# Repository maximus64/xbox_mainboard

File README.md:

# Xbox Original Mainboard Reverse Engineering

This project is an attempt to recreate the Xbox 1.6 mainboard in Kicad. The first goal is to recreate the layout of the PCB then recover the netlist then draw the schematic.

Note: [Custom version of Kicad](https://github.com/maximus64/kicad/tree/maximus/xbox_project) are required to load this project. The official version of Kicad has bitmap surface cache size limmiter and stores bitmap data as base64 encoded data. The patch removes the surface cache size constraint and just stores the image path rather than the store the bitmap data as base64 encoding. This is done to enhance performance so that Kicad can display the board scan overlay and re-trace the mainboard layout.

## Board scan

Scan image of all the copper layers is in kicad/xbox_1.6/board_scan/1.6

### PCB stackup

1. Signal
2. Ground
3. Power
4. Signal

### Progress

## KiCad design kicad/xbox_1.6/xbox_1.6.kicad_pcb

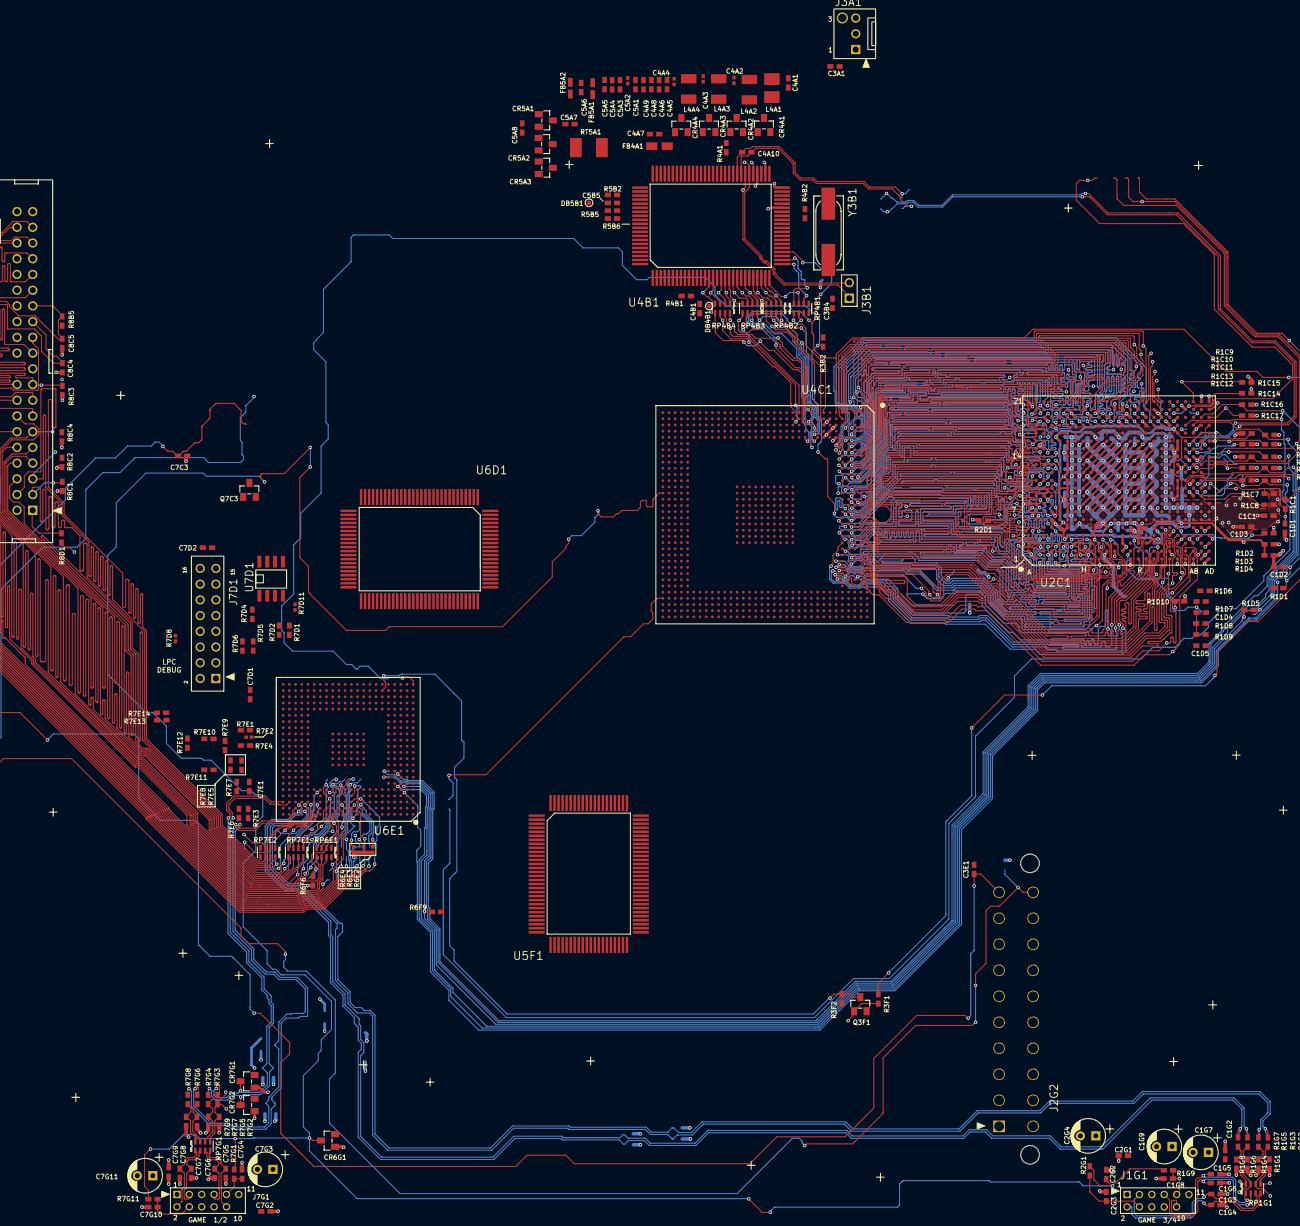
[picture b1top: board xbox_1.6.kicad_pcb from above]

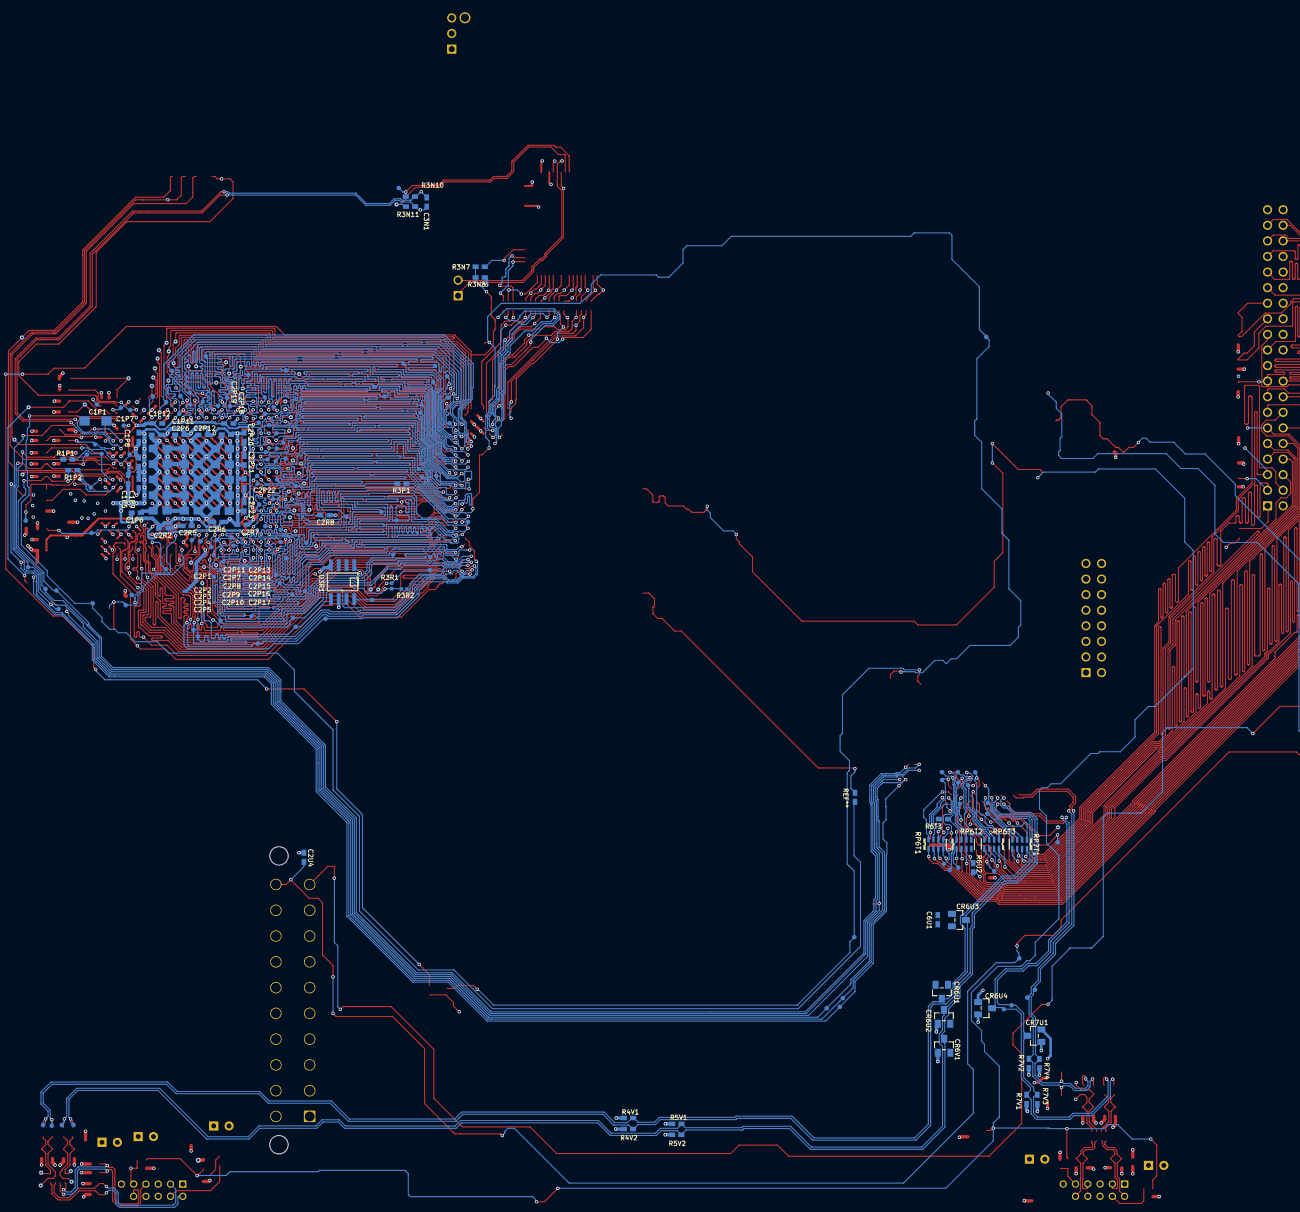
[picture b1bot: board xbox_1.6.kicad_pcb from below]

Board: 4 copper layers, 261 parts (69 on the bottom side), 273 nets.

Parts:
C1C1, C1D1, C1D2, C1D3, C1D4, C1D5, C1G2, C1G3, C1G4, C1G5, C1G6, C1G8, C1P5, C1P6, C1P7, C1P8, C1P9, C1P11, C1P12, C2G1, C2G2, C2G3, C2P6, C2P12, C2P18, C2P19, C2P20, C2P21, C2P22, C2P23, C2R2, C2R5, C2R6, C2R7, C2R8, C2U4, C3A1, C3B4, C3E1, C3N1, C4A1, C4A5, C4A6, C4A7, C4A8, C4A9, C4A10, C4B1, C5A1, C5A3, C5A4, C5A5, C5A6, C5A7, C5A8, C5B5, C6U1, C7C3, C7D1, C7D2, C7E1, C7G2, C7G4, C7G5, C7G6, C7G7, C7G8, C7G9, C7G10, C8C4, C8C5: 0603_smd
C1G7, C1G9, C2G4, C7G3, C7G11: CP_Radial_Tantal_D5.5mm_P2.50mm
C1P1: 1206_smd
C2P1, C2P2, C2P3, C2P4, C2P5, C2P7, C2P8, C2P9, C2P10, C2P11, C2P13, C2P14, C2P15, C2P16, C2P17: 0805_smd
C4A2, C4A3, C4A4, C5A2: 0402_smd
CR4A1, CR4A2, CR4A3, CR4A4, CR5A1, CR5A2, CR5A3, CR6G1, CR6U1, CR6U2, CR6U3, CR6U4, CR6V1, CR7G1, CR7G2, CR7U1: SOT-23
DB4B1, DB5B1: TP
FB4A1: fb_2_smd
FB5A1, FB5A2: fb_1_smd
J1G1, J7G1: jst_phd_12
J2G2: ATX_20PIN
J3A1: fan_connector
J3B1: PinHeader_1x02_P2.54mm_Vertical
J7D1: LPC_16_Pin
J8C1: IDC_40_Pin
L4A1: inductor_1210_bigpad_smd
L4A2, L4A3, L4A4: inductor_1210_smd
Q3F1, Q7C3: SOT-23
R1C1, R1C2, R1C3, R1C4, R1C5, R1C6, R1C7, R1C8, R1C9, R1C10, R1C11, R1C12, R1C13, R1C14, R1C15, R1C16, R1C17, R1D1, R1D2, R1D3, R1D4, R1D5, R1D6, R1D7, R1D8, R1D9, R1D10, R1G1, R1G2, R1G3, R1G4, R1G5, R1G6, R1G7, R1G8, R1G9, R1P1, R1P2, R2D1, R2G1, R3B2, R3F1, R3F2, R3N7, R3N8, R3N10, R3N11, R3P1, R4A1, R4B1, R4B2, R4V1, R4V2, R5B2, R5B5, R5B6, R5V1, R5V2, R6F6, R6F9, R6T3, R6U2, R7D1, R7D2, R7D4, R7D5, R7D6, R7E1, R7E3, R7E4, R7E5, R7E6, R7E7, R7E8, R7E9, R7E10, R7E11, R7E12, R7E13, R7E14, R7G1, R7G2, R7G3, R7G4, R7G5, R7G6, R7G7, R7G8, R7G9, R7G11, R7V1, R7V2, R7V3, R7V4, R8B5, R8C1, R8C2, R8C3, R8C4, R8D1: 0603_smd
R3R1, R3R2, R6E2, R6E3, R6E4, R7D8, R7D11, R7E2: 0402_smd
RP1G1, RP4B1, RP4B2, RP4B3, RP4B4, RP6E1, RP6T1, RP6T2, RP6T3, RP7E1, RP7E2, RP7G1, RP7T1: 0603_4_array
RT5A1: rt_1_smd
U2C1: intel_495_bga2
U3R1, U7D1: SOIC8
U4B1, U5F1, U6D1: ddr_100_tqfp
U4C1: nvidia_xgpu_nv2a
U6E1: nvidia_mcpx
Y3B1: Crystal_SMD_HC49-SD

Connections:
/5V: C7G2.1, C7G3.1, C7G9.1, C7G11.1, J2G2.15, J7G1.1, J7G1.8
/5V_STB: J2G2.1, J2G2.2, J2G2.3, J2G2.13
/CPU_A3: U2C1.L3, U4C1.B22
/CPU_A4: U2C1.K3, U4C1.A19
/CPU_A5: U2C1.J2, U4C1.D27
/CPU_A6: U2C1.L4, U4C1.A22
/CPU_A7: U2C1.L1, U4C1.C21
/CPU_A8: U2C1.K5, U4C1.A20
/CPU_A9: U2C1.K1, U4C1.B20
/CPU_A10: U2C1.J1, U4C1.A18
/CPU_A11: U2C1.J3, U4C1.B18
/CPU_A12: U2C1.K4, U4C1.C19
/CPU_A13: U2C1.G1, U4C1.C17
/CPU_A14: U2C1.H1, U4C1.A17
/CPU_A15: U2C1.E4, U4C1.D19
/CPU_A16: U2C1.F1, U4C1.A16
/CPU_A17: U2C1.F4, U4C1.D21
/CPU_A18: U2C1.F2, U4C1.C24
/CPU_A19: U2C1.E1, U4C1.E26
/CPU_A20: U2C1.C4, U4C1.E20
/CPU_A20M: R1P2.2, U2C1.AD10
/CPU_A20M_R: R1C6.1, R1P2.1, U6E1.H4
/CPU_A21: U2C1.D3, U4C1.E25
/CPU_A22: U2C1.D1, U4C1.D25
/CPU_A23: U2C1.E2, U4C1.C26
/CPU_A24: U2C1.D5, U4C1.E19
/CPU_A25: U2C1.D4, U4C1.C20
/CPU_A26: U2C1.C3, U4C1.E21
/CPU_A27: U2C1.C1, U4C1.E23
/CPU_A28: U2C1.B3, U4C1.C22
/CPU_A29: U2C1.A3, U4C1.B16
/CPU_A30: U2C1.B2, U4C1.E24
/CPU_ADS: U2C1.AB2, U4C1.B27
/CPU_BCLK: R3R1.2, R3R2.1, U2C1.M3
/CPU_BCLK_R: R3R1.1, U3R1.1, U4C1.C29
/CPU_BCLK_R2: R3R2.2, U3R1.8
/CPU_BNR: U2C1.T4, U4C1.C23
/CPU_BPRI: U2C1.U4, U4C1.E28
/CPU_BREQ0: R2D1.2, U2C1.C6
/CPU_BSEL0: R1C4.1, U2C1.AA12
/CPU_BSEL1: R1C10.1, U2C1.AB15
/CPU_CLKREF: C1D4.1, R1D8.1, R1D9.1, U2C1.P2
/CPU_D0: U2C1.D10, U4C1.A13
/CPU_D1: U2C1.D11, U4C1.D17
/CPU_D2: U2C1.C7, U4C1.E18
/CPU_D3: U2C1.C8, U4C1.E17
/CPU_D4: U2C1.B9, U4C1.A14
/CPU_D5: U2C1.A9, U4C1.B14
/CPU_D6: U2C1.C10, U4C1.A12
/CPU_D7: U2C1.B11, U4C1.B12
/CPU_D8: U2C1.C12, U4C1.C16
/CPU_D9: U2C1.B13, U4C1.A10
/CPU_D10: U2C1.A14, U4C1.A9
/CPU_D11: U2C1.B12, U4C1.E16
/CPU_D12: U2C1.E12, U4C1.A15
/CPU_D13: U2C1.B16, U4C1.C13
/CPU_D14: U2C1.A13, U4C1.B10
/CPU_D15: U2C1.D13, U4C1.C15
/CPU_D16: U2C1.D15, U4C1.E14
/CPU_D17: U2C1.D12, U4C1.D15
/CPU_D18: U2C1.B14, U4C1.C9
/CPU_D19: U2C1.E14, U4C1.C14
/CPU_D20: U2C1.C13, U4C1.A11
/CPU_D21: U2C1.A19, U4C1.C8
/CPU_D22: U2C1.B17, U4C1.A8
/CPU_D23: U2C1.A18, U4C1.E12
/CPU_D24: U2C1.C17, U4C1.E13
/CPU_D25: U2C1.D17, U4C1.D13
/CPU_D26: U2C1.C18, U4C1.A7
/CPU_D27: U2C1.B19, U4C1.C12
/CPU_D28: U2C1.D18, U4C1.B8
/CPU_D29: U2C1.B20, U4C1.B6
/CPU_D30: U2C1.A20, U4C1.A6
/CPU_D31: U2C1.B21, U4C1.A5
/CPU_D32: U2C1.D19, U4C1.E11
/CPU_D33: U2C1.C21, U4C1.C10
/CPU_D34: U2C1.E18, U4C1.E9
/CPU_D35: U2C1.C20, U4C1.D11
/CPU_D36: U2C1.F19, U4C1.C7
/CPU_D37: U2C1.D20, U4C1.D9
/CPU_D38: U2C1.D21, U4C1.E10
/CPU_D39: U2C1.H18, U4C1.C11
/CPU_D40: U2C1.F18, U4C1.E8
/CPU_D41: U2C1.J18, U4C1.C2
/CPU_D42: U2C1.F21, U4C1.A3
/CPU_D43: U2C1.E20, U4C1.B4
/CPU_D44: U2C1.H19, U4C1.A1
/CPU_D45: U2C1.E21, U4C1.A4
/CPU_D46: U2C1.J20, U4C1.C6
/CPU_D47: U2C1.H21, U4C1.B2
/CPU_D48: U2C1.L18, U4C1.C1
/CPU_D49: U2C1.G20, U4C1.C3
/CPU_D50: U2C1.P18, U4C1.E6
/CPU_D51: U2C1.G21, U4C1.A2
/CPU_D52: U2C1.K18, U4C1.E7
/CPU_D53: U2C1.K21, U4C1.C5
/CPU_D54: U2C1.M18, U4C1.C4
/CPU_D55: U2C1.L21, U4C1.D1
/CPU_D56: U2C1.R19, U4C1.E5
/CPU_D57: U2C1.K19, U4C1.D5
/CPU_D58: U2C1.T20, U4C1.E2
/CPU_D59: U2C1.J21, U4C1.D7
/CPU_D60: U2C1.L20, U4C1.E3
/CPU_D61: U2C1.M19, U4C1.E1
/CPU_D62: U2C1.U18, U4C1.E4
/CPU_D63: U2C1.R18, U4C1.D3
/CPU_DBSY: U2C1.AA3, U4C1.A28
/CPU_DEFER: U2C1.U3, U4C1.A24
/CPU_DRDY: U2C1.T1, U4C1.D28
/CPU_EDGECTRLP: R1C9.2, U2C1.AA16
/CPU_FERR: R1C5.1, R6F9.1, U2C1.AC12, U6E1.G5
/CPU_FLUSH: R1C8.1, U2C1.AC9
/CPU_HIT: U2C1.V1, U4C1.A25
/CPU_HITM: U2C1.Y4, U4C1.C27
/CPU_IGNNE: R1C11.2, U2C1.AC13, U6E1.H5
/CPU_INIT: R1C12.1, U2C1.AA10
/CPU_INTR_LINT0: R1C2.1, R1D5.2, U2C1.AB18
/CPU_INTR_LINT0_R: R1D5.1, U6E1.F2
/CPU_LOCK: U2C1.R1, U4C1.C28
/CPU_NMI_LINT1: R1C16.1, R1D1.2, U2C1.AC19
/CPU_NMI_LINT1_R: R1D1.1, U6E1.E3
/CPU_PICD0: R1C15.1, U2C1.AB21
/CPU_PICD1: R1C14.1, U2C1.Y20
/CPU_REQ0: U2C1.T2, U4C1.E27
/CPU_REQ1: U2C1.V4, U4C1.C25
/CPU_REQ2: U2C1.V2, U4C1.B24
/CPU_REQ3: U2C1.W3, U4C1.A26
/CPU_REQ4: U2C1.W5, U4C1.A27
/CPU_RESET: C2R8.1, R3P1.1, U2C1.A6
/CPU_RESET_R: R3B2.1, R3P1.2, U4C1.C18, U6E1.AB1
/CPU_RS0: U2C1.U1, U4C1.A23
/CPU_RS1: U2C1.AA2, U4C1.B28
/CPU_RS2: U2C1.W1, U4C1.B26
/CPU_RTTIMPEDP: R1C17.1, U2C1.AD19
/CPU_SLP: R1C13.1, U2C1.AB12
/CPU_SMI: C1D1.2, R1C1.1, R1C7.1, U2C1.AB10
/CPU_SMI_R: C1D2.2, R1C1.2, U6E1.F3
/CPU_STPCLK: R1P1.2, U2C1.AC11
/CPU_TESTHI: R1C3.1, U2C1.AD17
/CPU_TESTLO1: R1D2.1, U2C1.Y5
/CPU_TESTLO2: R1D10.1, U2C1.N5
/CPU_THERMDA: C3N1.1, R3N10.2, U2C1.AA15
/CPU_THERMDA_R: C4A10.1, R3N10.1, U4B1.59
/CPU_THERMDC: C3N1.2, R3N11.2, U2C1.AB16
/CPU_THERMDC_R: C4A10.2, R3N11.1, U4B1.58
/CPU_TRDY: U2C1.U2, U4C1.E22
/CPU_VCC: C2P1.2, C2P2.2, C2P3.2, C2P4.2, C2P5.2, C2P7.2, C2P8.2, C2P9.2, C2P10.2, C2P11.2, C2P13.2, C2P14.2, C2P15.2, C2P16.2, C2P17.2, U2C1.H8, U2C1.H10, U2C1.H12, U2C1.H14, U2C1.H16, U2C1.J7, U2C1.J9, U2C1.J11, U2C1.J13, U2C1.J15, U2C1.K8, U2C1.K10, U2C1.K12, U2C1.K14, U2C1.K16, U2C1.L7, U2C1.L9, U2C1.L11, U2C1.L13, U2C1.L15, U2C1.M8, U2C1.M10, U2C1.M12, U2C1.M14, U2C1.M16, U2C1.N7, U2C1.N9, U2C1.N11, U2C1.N13, U2C1.N15, U2C1.P8, U2C1.P10, U2C1.P12, U2C1.P14, U2C1.P16, U2C1.R7, U2C1.R9, U2C1.R11, U2C1.R13, U2C1.R15, U2C1.T8, U2C1.T10, U2C1.T12, U2C1.T14, U2C1.T16, U2C1.U7, U2C1.U9, U2C1.U11, U2C1.U13, U2C1.U15
/CPU_VCCT: C1C1.2, C1D3.2, C1P5.2, C1P7.2, C1P8.2, C1P9.2, C1P11.2, C2P6.2, C2P12.2, C2P18.2, C2P20.2, C2P21.2, C2P22.2, C2P23.2, C2R2.2, C2R5.2, C2R6.2, C2R7.2, R1C2.2, R1C3.2, R1C4.2, R1C5.2, R1C6.2, R1C7.2, R1C8.2, R1C10.2, R1C11.1, R1C12.2, R1C13.2, R1C14.2, R1C15.2, R1C16.2, R1D3.2, R1P1.1, U2C1.AA6, U2C1.AA7, U2C1.AA8, U2C1.AB6, U2C1.AB7, U2C1.AB8, U2C1.AC6, U2C1.AC7, U2C1.AC8, U2C1.AD6, U2C1.AD7, U2C1.AD8, U2C1.G6, U2C1.G7, U2C1.G8, U2C1.G9, U2C1.G10, U2C1.G11, U2C1.G12, U2C1.G13, U2C1.G14, U2C1.G15, U2C1.G16, U2C1.G17, U2C1.H6, U2C1.H17, U2C1.J6, U2C1.J17, U2C1.K6, U2C1.K17, U2C1.L6, U2C1.L17, U2C1.M6, U2C1.M17, U2C1.N6, U2C1.N17, U2C1.P6, U2C1.P17, U2C1.R6, U2C1.R17, U2C1.T6, U2C1.T17, U2C1.U6, U2C1.U17, U2C1.V6, U2C1.V7, U2C1.V8, U2C1.V9, U2C1.V10, U2C1.V11, U2C1.V12, U2C1.V13, U2C1.V14, U2C1.V15, U2C1.V16, U2C1.V17, U2C1.W6, U2C1.W7, U2C1.W8, U2C1.W9, U2C1.W10, U2C1.W11, U2C1.W12, U2C1.W13, U2C1.W14, U2C1.W15, U2C1.W16, U2C1.W17, U2C1.Y6, U2C1.Y7, U2C1.Y8
/CPU_VREF: C1P6.2, C1P12.2, C2P19.2, R1D3.1, R1D4.1, U2C1.AA9, U2C1.AD18, U2C1.E5, U2C1.E16, U2C1.E17, U2C1.F5, U2C1.F17, U2C1.U5, U2C1.Y17, U2C1.Y18
/GAME1_VSYNC: C7G10.2, J7G1.4, R7G11.2
/GAME2_VSYNC: C7G4.1, J7G1.9, R7G1.1
/GAME3_VBUS: C1G2.1, C1G7.1, J1G1.1
/GAME3_VSYNC: C2G3.1, J1G1.4, R2G1.1
/GAME4_VBUS: C1G9.1, C2G1.2, J1G1.8
/GAME4_VSYNC: C1G8.2, J1G1.9, R1G9.2
/IDE_11_R: RP7E1.4, U6E1.B16
/IDE_A0: J8C1.35, RP6T1.3
/IDE_A0_R: RP6T1.6, U6E1.C12
/IDE_A1: J8C1.33, RP6T2.1
/IDE_A2: J8C1.36, RP6T1.4
/IDE_CS0: J8C1.37, RP6T1.1
/IDE_CS0_R: RP6T1.8, U6E1.C11
/IDE_CS1: J8C1.38, RP6T1.2
/IDE_CS1_R: RP6T1.7, U6E1.D11
/IDE_D0: J8C1.17, R8C3.2, RP6E1.6
/IDE_D0_R: RP6E1.3, U6E1.A14
/IDE_D1: J8C1.15, RP6T3.6
/IDE_D1_R: RP6T3.3, U6E1.E14
/IDE_D2: J8C1.13, RP6T3.8
/IDE_D2_R: RP6T3.1, U6E1.C15
/IDE_D3: J8C1.11, R8C4.2, RP7E1.7
/IDE_D3_R: RP7E1.2, U6E1.A15
/IDE_D4: J8C1.9, RP7T1.5
/IDE_D4_R: RP7T1.4, U6E1.D15
/IDE_D5: J8C1.7, RP7T1.6
/IDE_D6: J8C1.5, R8C2.2, RP7E2.7
/IDE_D6_R: RP7E2.2, U6E1.B17
/IDE_D7: J8C1.3, R8C1.2, RP7E2.8
/IDE_D7_R: RP7E2.1, U6E1.A17
/IDE_D8: J8C1.4, RP7E2.6
/IDE_D8_R: RP7E2.3, U6E1.A18
/IDE_D9: J8C1.6, RP7T1.8
/IDE_D9_R: RP7T1.1, U6E1.C17
/IDE_D10: J8C1.8, RP7T1.7
/IDE_D10_R: RP7T1.2, U6E1.E16
/IDE_D11: J8C1.10, RP7E1.5
/IDE_D12: J8C1.12, RP7E1.8
/IDE_D12_R: RP7E1.1, U6E1.E15
/IDE_D13: J8C1.14, RP7E1.6
/IDE_D13_R: RP7E1.3, U6E1.B15
/IDE_D14: J8C1.16, RP6T3.7
/IDE_D14_R: RP6T3.2, U6E1.D14
/IDE_D15: J8C1.18, RP6E1.5
/IDE_D15_R: RP6E1.4, U6E1.C14
/IDE_DIOR: C8C4.2, J8C1.25, R6U2.2
/IDE_DIOR_R: R6U2.1, U6E1.C13
/IDE_DIOW: J8C1.23, RP6T3.5
/IDE_DIOW_R: RP6T3.4, U6E1.E13
/IDE_DMACK: J8C1.29, RP6T2.3
/IDE_DMACK_R: RP6T2.6, U6E1.D12
/IDE_DMARQ: J8C1.21, RP6E1.7
/IDE_DMARQ_R: R6F6.2, RP6E1.2, U6E1.B14
/IDE_INTRQ: J8C1.31, RP6T2.2
/IDE_INTRQ_R: R6T3.2, RP6T2.7, U6E1.E12
/IDE_IORDY: C8C5.2, J8C1.27, R8B5.2, U6E1.B13
/IDE_RESET: J8C1.1, R8D1.2
/NB_F1: R3F1.2, R3N7.1, R3N8.1, U4C1.F1
/NB_F1_R: Q3F1.1, R3F1.1
/NB_F1_R2: R3N7.2, U4B1.34
/NB_F1_R_TRAN_3: Q3F1.3, R3F2.2, U6E1.AA6
/NB_VCC1: U4C1.AA22, U4C1.AB13, U4C1.AB15, U4C1.AB17, U4C1.AB19, U4C1.AB21, U4C1.N14, U4C1.N16, U4C1.N18, U4C1.N20, U4C1.N22, U4C1.P13, U4C1.R22, U4C1.T13, U4C1.U22, U4C1.V13, U4C1.W22, U4C1.Y13
/NB_VSYNC: C2G2.1, R1G9.1, R2G1.2, R7G1.2, R7G11.1, U4C1.AP14
/PIXEL_CLK: RP4B1.8, U4B1.32
/PIXEL_CLK_R: RP4B1.1, U4C1.H1
/PIXEL_D0: RP4B2.1, U4B1.29
/PIXEL_D0_R: RP4B2.8, U4C1.H4
/PIXEL_D1: RP4B2.2, U4B1.28
/PIXEL_D1_R: RP4B2.7, U4C1.J5
/PIXEL_D2: RP4B2.3, U4B1.27
/PIXEL_D2_R: RP4B2.6, U4C1.K5
/PIXEL_D3: RP4B2.4, U4B1.26
/PIXEL_D3_R: RP4B2.5, U4C1.J3
/PIXEL_D4: RP4B3.1, U4B1.24
/PIXEL_D4_R: RP4B3.8, U4C1.J4
/PIXEL_D5: RP4B3.2, U4B1.22
/PIXEL_D5_R: RP4B3.7, U4C1.L5
/PIXEL_D6: RP4B3.3, U4B1.21
/PIXEL_D6_R: RP4B3.6, U4C1.M2
/PIXEL_D7: RP4B3.4, U4B1.20
/PIXEL_D7_R: RP4B3.5, U4C1.J1
/PIXEL_D8: RP4B4.1, U4B1.19
/PIXEL_D8_R: RP4B4.8, U4C1.K3
/PIXEL_D9: RP4B4.2, U4B1.18
/PIXEL_D9_R: RP4B4.7, U4C1.M1
/PIXEL_D10: RP4B4.3, U4B1.16
/PIXEL_D11: RP4B4.4, U4B1.15
/PIXEL_D11_R: RP4B4.5, U4C1.L3
/PIXEL_HSYNC: RP4B1.7, U4B1.30
/PIXEL_HSYNC_R: RP4B1.2, U4C1.K1
/PIXEL_VSYNC: RP4B1.6, U4B1.31
/PIXEL_VSYNC_R: RP4B1.3, U4C1.L1
/POWER_OK: C3E1.1, C7C3.1, J2G2.10
/POWER_ON: C2U4.1, J2G2.20
/SB_A11: R6E3.2, U6E1.A11
/SB_B10: R6E2.2, U6E1.B10
/SB_B11: R6E4.2, U6E1.B11
/USB1_N: CR6U4.3, R7G8.2, R7V1.2, U6E1.B20
/USB1_P: CR7U1.3, R7G6.2, R7V3.2, U6E1.A20
/USB1_R2_N: C7G8.2, J7G1.2, RP7G1.1
/USB1_R2_P: C7G7.2, J7G1.3, RP7G1.2
/USB1_R_N: R7G8.1, R7G9.2, RP7G1.8
/USB1_R_P: R7G6.1, R7G7.2, RP7G1.7
/USB2_N: CR7G2.3, R7G4.2, U6E1.C21
/USB2_P: CR7G1.3, R7G3.2, U6E1.C22
/USB2_R2_N: C7G6.2, J7G1.7, RP7G1.3
/USB2_R2_P: C7G5.2, J7G1.10, RP7G1.4
/USB2_R_N: R7G4.1, R7G5.2, RP7G1.6
/USB2_R_P: R7G2.2, R7G3.1, RP7G1.5
/USB3_N: CR6U1.3, R1G2.2, R4V1.2, U6E1.C18
/USB3_P: CR6U3.3, R1G3.2, R4V2.2, U6E1.B18
/USB3_R2_N: C1G4.1, J1G1.2, RP1G1.4
/USB3_R2_P: C1G3.1, J1G1.3, RP1G1.3
/USB3_R_N: R1G1.2, R1G2.1, RP1G1.5
/USB3_R_P: R1G3.1, R1G4.2, RP1G1.6
/USB4_N: CR6U2.3, R1G5.2, R5V1.2, U6E1.C19
/USB4_P: CR6V1.3, R1G7.2, R5V2.2, U6E1.B19
/USB4_R2_N: C1G6.1, J1G1.7, RP1G1.2
/USB4_R2_P: C1G5.1, J1G1.10, RP1G1.1
/USB4_R_N: R1G5.1, R1G6.2, RP1G1.7
/USB4_R_P: R1G7.1, R1G8.2, RP1G1.8
/VSS: C1C1.1, C1D1.1, C1D2.1, C1D3.1, C1D4.2, C1G2.2, C1G3.2, C1G4.2, C1G5.2, C1G6.2, C1G7.2, C1G8.1, C1G9.2, C1P1.1, C1P5.1, C1P6.1, C1P7.1, C1P8.1, C1P9.1, C1P11.1, C1P12.1, C2G1.1, C2G2.2, C2G3.2, C2P1.1, C2P2.1, C2P3.1, C2P4.1, C2P5.1, C2P6.1, C2P7.1, C2P8.1, C2P9.1, C2P10.1, C2P11.1, C2P12.1, C2P13.1, C2P14.1, C2P15.1, C2P16.1, C2P17.1, C2P18.1, C2P19.1, C2P20.1, C2P21.1, C2P22.1, C2P23.1, C2R2.1, C2R5.1, C2R6.1, C2R7.1, C2R8.2, C2U4.2, C3E1.2, C7C3.2, C7G2.2, C7G3.2, C7G4.2, C7G5.1, C7G6.1, C7G7.1, C7G8.1, C7G9.2, C7G10.1, C7G11.2, C8C4.1, C8C5.1, CR6G1.1, CR6U2.1, CR6U4.1, CR6V1.1, CR7G1.1, CR7G2.1, CR7U1.1, J2G2.4, J2G2.5, J2G2.6, J2G2.9, J2G2.12, J2G2.14, J2G2.16, J2G2.19, J7G1.5, J7G1.6, J7G1.11, J8C1.2, J8C1.19, J8C1.22, J8C1.40, R1C9.1, R1C17.2, R1D2.2, R1D4.2, R1D8.2, R1D10.2, R1G1.1, R1G4.1, R1G6.1, R1G8.1, R2D1.1, R3N8.2, R4V1.1, R4V2.1, R5V1.1, R5V2.1, R6F6.1, R7G2.1, R7G5.1, R7G7.1, R7G9.1, R7V1.1, R7V2.2, R7V3.1, R7V4.2, R8C1.1, R8C2.1, R8C3.1, R8C4.1, U2C1.A2, U2C1.A7, U2C1.A8, U2C1.A12, U2C1.A21, U2C1.AA4, U2C1.AA13, U2C1.AA20, U2C1.AB3, U2C1.AB4, U2C1.AB5, U2C1.AB9, U2C1.AB11, U2C1.AB13, U2C1.AB14, U2C1.AB17, U2C1.AC1, U2C1.AC2, U2C1.AC4, U2C1.AC5, U2C1.AC10, U2C1.AC14, U2C1.AC16, U2C1.AC18, U2C1.AC21, U2C1.AD1, U2C1.AD2, U2C1.AD3, U2C1.AD4, U2C1.AD5, U2C1.AD16, U2C1.AD21, U2C1.B1, U2C1.B5, U2C1.B6, U2C1.B7, U2C1.B8, U2C1.B10, U2C1.B15, U2C1.B18, U2C1.C9, U2C1.C11, U2C1.C15, U2C1.C16, U2C1.C19, U2C1.D2, U2C1.D6, U2C1.D7, U2C1.D9, U2C1.E3, U2C1.E7, U2C1.E8, U2C1.E9, U2C1.E10, U2C1.E11, U2C1.E13, U2C1.E19, U2C1.F3, U2C1.F6, U2C1.F7, U2C1.F8, U2C1.F9, U2C1.F10, U2C1.F11, U2C1.F12, U2C1.F13, U2C1.F14, U2C1.F15, U2C1.F16, U2C1.F20, U2C1.G3, U2C1.G19, U2C1.H2, U2C1.H7, U2C1.H9, U2C1.H11, U2C1.H13, U2C1.H15, U2C1.H20, U2C1.J4, U2C1.J8, U2C1.J10, U2C1.J12, U2C1.J14, U2C1.J16, U2C1.J19, U2C1.K2, U2C1.K7, U2C1.K9, U2C1.K11, U2C1.K13, U2C1.K15, U2C1.K20, U2C1.L5, U2C1.L8, U2C1.L10, U2C1.L12, U2C1.L14, U2C1.L16, U2C1.L19, U2C1.M7, U2C1.M9, U2C1.M11, U2C1.M13, U2C1.M15, U2C1.M20, U2C1.N2, U2C1.N3, U2C1.N4, U2C1.N8, U2C1.N10, U2C1.N12, U2C1.N14, U2C1.N16, U2C1.N18, U2C1.N19, U2C1.N20, U2C1.P1, U2C1.P5, U2C1.P7, U2C1.P9, U2C1.P11, U2C1.P13, U2C1.P15, U2C1.P19, U2C1.R3, U2C1.R4, U2C1.R5, U2C1.R8, U2C1.R10, U2C1.R12, U2C1.R14, U2C1.R16, U2C1.R20, U2C1.T3, U2C1.T5, U2C1.T7, U2C1.T9, U2C1.T11, U2C1.T13, U2C1.T15, U2C1.T18, U2C1.T19, U2C1.U8, U2C1.U10, U2C1.U12, U2C1.U14, U2C1.U16, U2C1.U20, U2C1.V3, U2C1.V19, U2C1.W4, U2C1.W18, U2C1.Y3, U2C1.Y9, U2C1.Y10, U2C1.Y11, U2C1.Y12, U2C1.Y13, U2C1.Y14, U2C1.Y15, U2C1.Y16, U2C1.Y19, U3R1.4, U4B1.45, U4B1.50, U4B1.52, U4B1.54, U4C1.AA13, U4C1.AA14, U4C1.AA15, U4C1.AA16, U4C1.AA17, U4C1.AA18, U4C1.AA19, U4C1.AA20, U4C1.AA21, U4C1.AB14, U4C1.AB16, U4C1.AB18, U4C1.AB20, U4C1.AB22, U4C1.B1, U4C1.F3, U4C1.F5, U4C1.G2, U4C1.G4, U4C1.H3, U4C1.H5, U4C1.N13, U4C1.N15, U4C1.N17, U4C1.N19, U4C1.N21, U4C1.P14, U4C1.P15, U4C1.P16, U4C1.P17, U4C1.P18, U4C1.P19, U4C1.P20, U4C1.P21, U4C1.P22, U4C1.R13, U4C1.R14, U4C1.R15, U4C1.R16, U4C1.R17, U4C1.R18, U4C1.R19, U4C1.R20, U4C1.R21, U4C1.T14, U4C1.T15, U4C1.T16, U4C1.T17, U4C1.T18, U4C1.T19, U4C1.T20, U4C1.T21, U4C1.T22, U4C1.U13, U4C1.U14, U4C1.U15, U4C1.U16, U4C1.U17, U4C1.U18, U4C1.U19, U4C1.U20, U4C1.U21, U4C1.V14, U4C1.V15, U4C1.V16, U4C1.V17, U4C1.V18, U4C1.V19, U4C1.V20, U4C1.V21, U4C1.V22, U4C1.W13, U4C1.W14, U4C1.W15, U4C1.W16, U4C1.W17, U4C1.W18, U4C1.W19, U4C1.W20, U4C1.W21, U4C1.Y14, U4C1.Y15, U4C1.Y16, U4C1.Y17, U4C1.Y18, U4C1.Y19, U4C1.Y20, U4C1.Y21, U4C1.Y22
UNK_0001: J3B1.1, U4B1.57
UNK_0002: J3B1.2, U4B1.56

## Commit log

2022-12-09 route more traces
2022-12-09 route more
2022-12-16 wip auto tracer
2022-12-17 add 0603 footprint
2022-12-17 add some footprints
2022-12-18 front CPU area mostly finish
2022-12-19 start to route IDE port
2022-12-25 route more ide
2022-12-31 change thermal relief
2022-12-31 route some NB signals
2023-01-01 route more USB + IDE
2023-01-01 add 0402 smd footprint
2023-01-01 add board scan files
2023-01-01 fix NB_VSYNC and route more USB signals
2023-01-01 route game port 3/4
2023-01-02 route pixel bus + usb for controller port
2023-01-03 route more cpu signal on the back side
2023-01-03 route more cpu back
2023-01-03 route more CPU traces
2023-01-04 route more cpu signals
2023-01-18 update PLL ic partnum
2023-03-26 wip 25032023
2023-04-07 wip 4/7/2023
2023-04-07 random craps
2023-04-15 clean up. Correct board scan path and move under project
2023-04-15 remove junks
2023-04-15 Add README
